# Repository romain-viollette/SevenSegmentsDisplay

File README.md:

SevenSegmentsDisplay
====================

description: Autonomous 3 seven-segments display powered by an Atmega328P.

author: Romain VIOLLETTE romain.viollette@gmail.com

https://github.com/romain-viollette/SevenSegmentsDisplay

http://www.oshpark.com/shared_projects/W5Fzhe9d - http://www.oshpark.com/profiles/RomainViollette

.JPG)

features:
  - small form factor
  - communication: Serial, I2C, SPI, (bitbanging possible if you want to) 
  - SDM components, soldering by hand is not too difficult.
  - 5 volts only
  - Arduino IDE compatible
  - programmable via ISP by default (or maybe via serial lines with a different bootloader)
  - crystal 16Mhz, 20MHz (or whatever or internal if you want to) 
  - 2 support holes for 3 mm screws

partlist: (See complete file in /version_xx/eagle/partlist.txt)
  - PCB at OSHpark.com see http://www.oshpark.com/profiles/RomainViollette
  - 3 x TDSO 5151 - Seven Segments displays with common cathode (any common cathode 7 seg display would fit)
  - 2 leds, any basic ones would fit, adapt R5 and R6 for current limiting.
  - SMD discrete parts form factor 0805:
      - C1 & C3 - 100nF - unpolarized decoupling capacitor
      - C4 & C5 - 12-22pF - unpolarized capacitor for quartz
      - ATMEGA328P-AU - TQFP32 - http://bit.ly/1gV6cmJ
      - QUARTZ - MULTICOMP HC49SM-20-30-50-60-16-ATF - http://bit.ly/1i76kLW
      - R2, R3 & R4 - 150 Ohms - current limiting resistor for 7 seg displays (adapt them to your display specs)
      - R5 & R6 - 150-2200 Ohms  - current limiting resistor for LED (adapt them to your LED specs)
      - R1 - !!!ERROR!!! - do not put anything - R1 could be used as a reset switch (I set R1 as pulldown instead of pullup)
	  
notice:
	- If you beggin in SMD, consider buying http://bit.ly/1ikUmQc and the equivalent for capacitor: you  will save a lot of money at the end.
	- R1 is wrong, see in Partlist.
	- Connectors should be placed on the same side than led display. If you want to put the connector on the other side like I did in the photos (http://bit.ly/1hbSIUK), keep in mind that the pinning is inverted.
	- There is not power regulator, nor overvoltage protection, so nerver power with more than 5V. (Maybe 3.3 could works?).

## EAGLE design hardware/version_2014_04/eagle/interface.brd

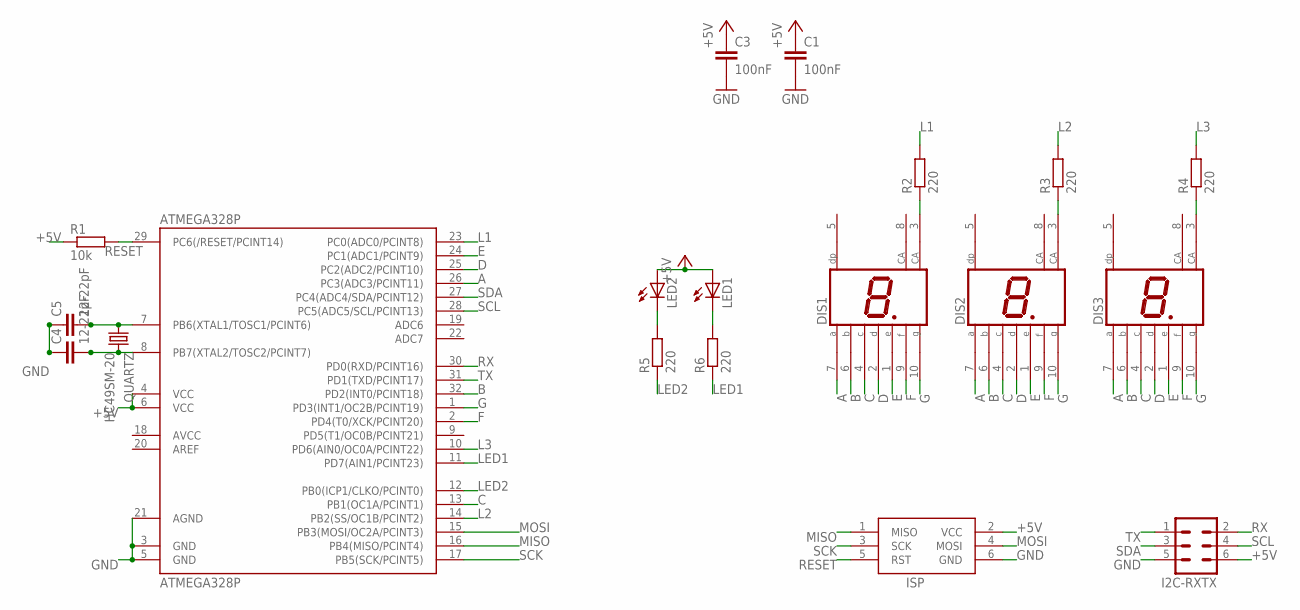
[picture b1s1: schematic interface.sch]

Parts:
ATMEGA328P: ATMEGA328P; TQFP32-08
C1, C3: 100nF; C0805
C4, C5: 12-22pF; C0805
DIS1, DIS2, DIS3: HD-H101; HDSP-M
I2C-RXTX: MA03-2
ISP: AVRISP-6; AVRISP
LED1, LED2: LED5MM
QUARTZ: HC49SM-20; HC49UP
R1: 10k; R0805
R2, R3, R4, R5, R6: 220; R0805

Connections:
+5V: ATMEGA328P.4 (VCC), ATMEGA328P.6 (VCC), C1.1, C3.1, I2C-RXTX.6, ISP.2 (VCC), LED1.A, LED2.A, R1.1
A: ATMEGA328P.26 (PC3(ADC3/PCINT11)), DIS1.7 (A), DIS2.7 (A), DIS3.7 (A)
B: ATMEGA328P.32 (PD2(INT0/PCINT18)), DIS1.6 (B), DIS2.6 (B), DIS3.6 (B)
C: ATMEGA328P.13 (PB1(OC1A/PCINT1)), DIS1.4 (C), DIS2.4 (C), DIS3.4 (C)
D: ATMEGA328P.25 (PC2(ADC2/PCINT10)), DIS1.2 (D), DIS2.2 (D), DIS3.2 (D)
E: ATMEGA328P.24 (PC1(ADC1/PCINT9)), DIS1.1 (E), DIS2.1 (E), DIS3.1 (E)
F: ATMEGA328P.2 (PD4(T0/XCK/PCINT20)), DIS1.9 (F), DIS2.9 (F), DIS3.9 (F)
G: ATMEGA328P.1 (PD3(INT1/OC2B/PCINT19)), DIS1.10 (G), DIS2.10 (G), DIS3.10 (G)
GND: ATMEGA328P.3 (GND), ATMEGA328P.5 (GND), ATMEGA328P.21 (AGND), C1.2, C3.2, C4.1, C5.1, I2C-RXTX.5, ISP.6 (GND)
L1: ATMEGA328P.23 (PC0(ADC0/PCINT8)), R2.2
L2: ATMEGA328P.14 (PB2(SS/OC1B/PCINT2)), R3.2
L3: ATMEGA328P.10 (PD6(AIN0/OC0A/PCINT22)), R4.2
LED1: ATMEGA328P.11 (PD7(AIN1/PCINT23)), R6.1
LED2: ATMEGA328P.12 (PB0(ICP1/CLKO/PCINT0)), R5.1
MISO: ATMEGA328P.16 (PB4(MISO/PCINT4)), ISP.1 (MISO)
MOSI: ATMEGA328P.15 (PB3(MOSI/OC2A/PCINT3)), ISP.4 (MOSI)
unnamed: ATMEGA328P.8 (PB7(XTAL2/TOSC2/PCINT7)), C4.2, QUARTZ.2
unnamed: ATMEGA328P.7 (PB6(XTAL1/TOSC1/PCINT6)), C5.2, QUARTZ.1
unnamed: DIS2.3 (CA), R3.1
unnamed: DIS3.3 (CA), R4.1
unnamed: LED2.K (C), R5.2
unnamed: DIS1.3 (CA), R2.1
unnamed: LED1.K (C), R6.2
RESET: ATMEGA328P.29 (PC6(/RESET/PCINT14)), ISP.5 (RST), R1.2
RX: ATMEGA328P.30 (PD0(RXD/PCINT16)), I2C-RXTX.2
SCK: ATMEGA328P.17 (PB5(SCK/PCINT5)), ISP.3 (SCK)
SCL: ATMEGA328P.28 (PC5(ADC5/SCL/PCINT13)), I2C-RXTX.4
SDA: ATMEGA328P.27 (PC4(ADC4/SDA/PCINT12)), I2C-RXTX.3
TX: ATMEGA328P.31 (PD1(TXD/PCINT17)), I2C-RXTX.1

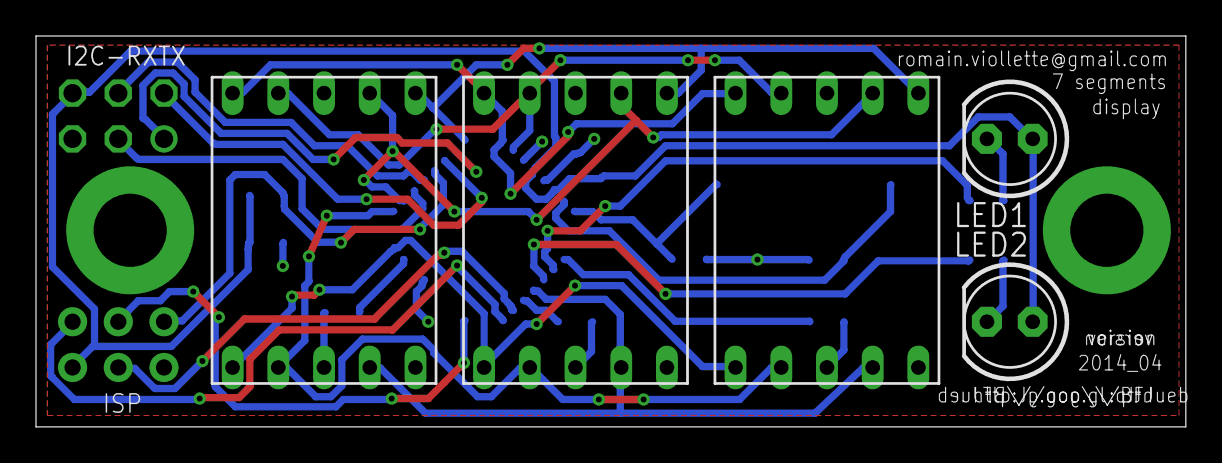
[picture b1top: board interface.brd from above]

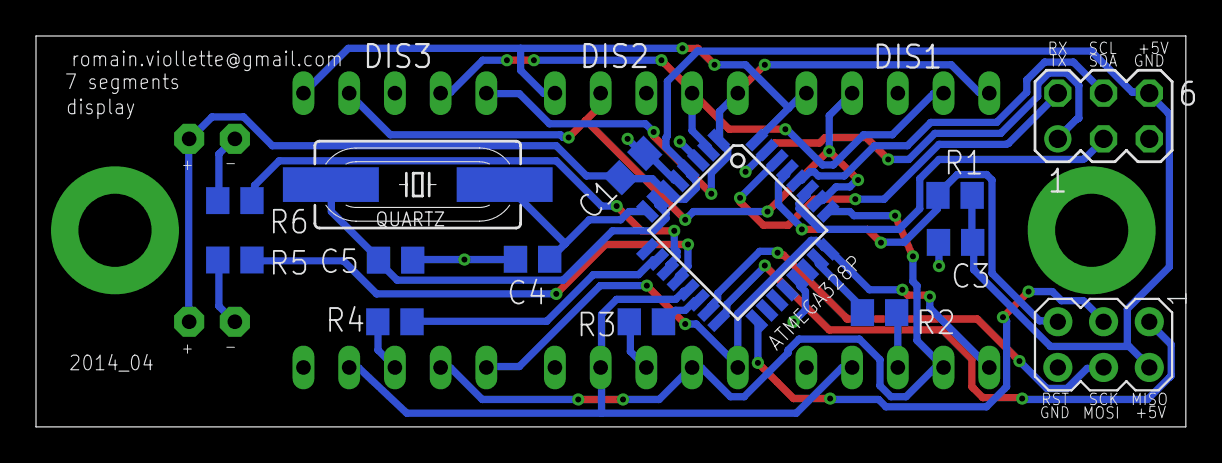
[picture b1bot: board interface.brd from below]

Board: 2 copper layers, 63.9 x 21.7 mm, 19 parts (14 on the bottom side), 29 nets.

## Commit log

2014-04-04 first commit - hardware version 2013_11
2014-04-04 photo of version 2013_11
2014-04-04 added datasheets
2014-04-04 added raw software files
    arduino IDE >= 1.0
2014-04-04 added top and bottom pcb image for version 2013_11
2014-04-04 edit oshpark link
2014-04-04 folder structure changed
2014-04-04 corrected polarization of display
2014-04-04 version 2013_11 was in fact newer, now corrected
2014-04-04 correction of resistor R1 mistake
2014-04-04 changing placing side of ISP connector
2014-04-04 mirrored RXTX connector
2014-04-19 added photos to readme
